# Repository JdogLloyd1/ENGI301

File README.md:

# ENGI301
Repository for ENGI301 course work Fall 2022

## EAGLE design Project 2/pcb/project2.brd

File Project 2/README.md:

# ENGI301
Repository for ENGI301 Project 2 - create a PCB that interfaces with PocketBeagle for an electronic Etch-A-Sketch. 

Repository includes PowerPoint presentation with mechanical system overview, EAGLE library/schematic/layout files, and necessary manufacturing information. 

Bill of material and manufacturing quotes from MacroFab can be found in the documentation folder.

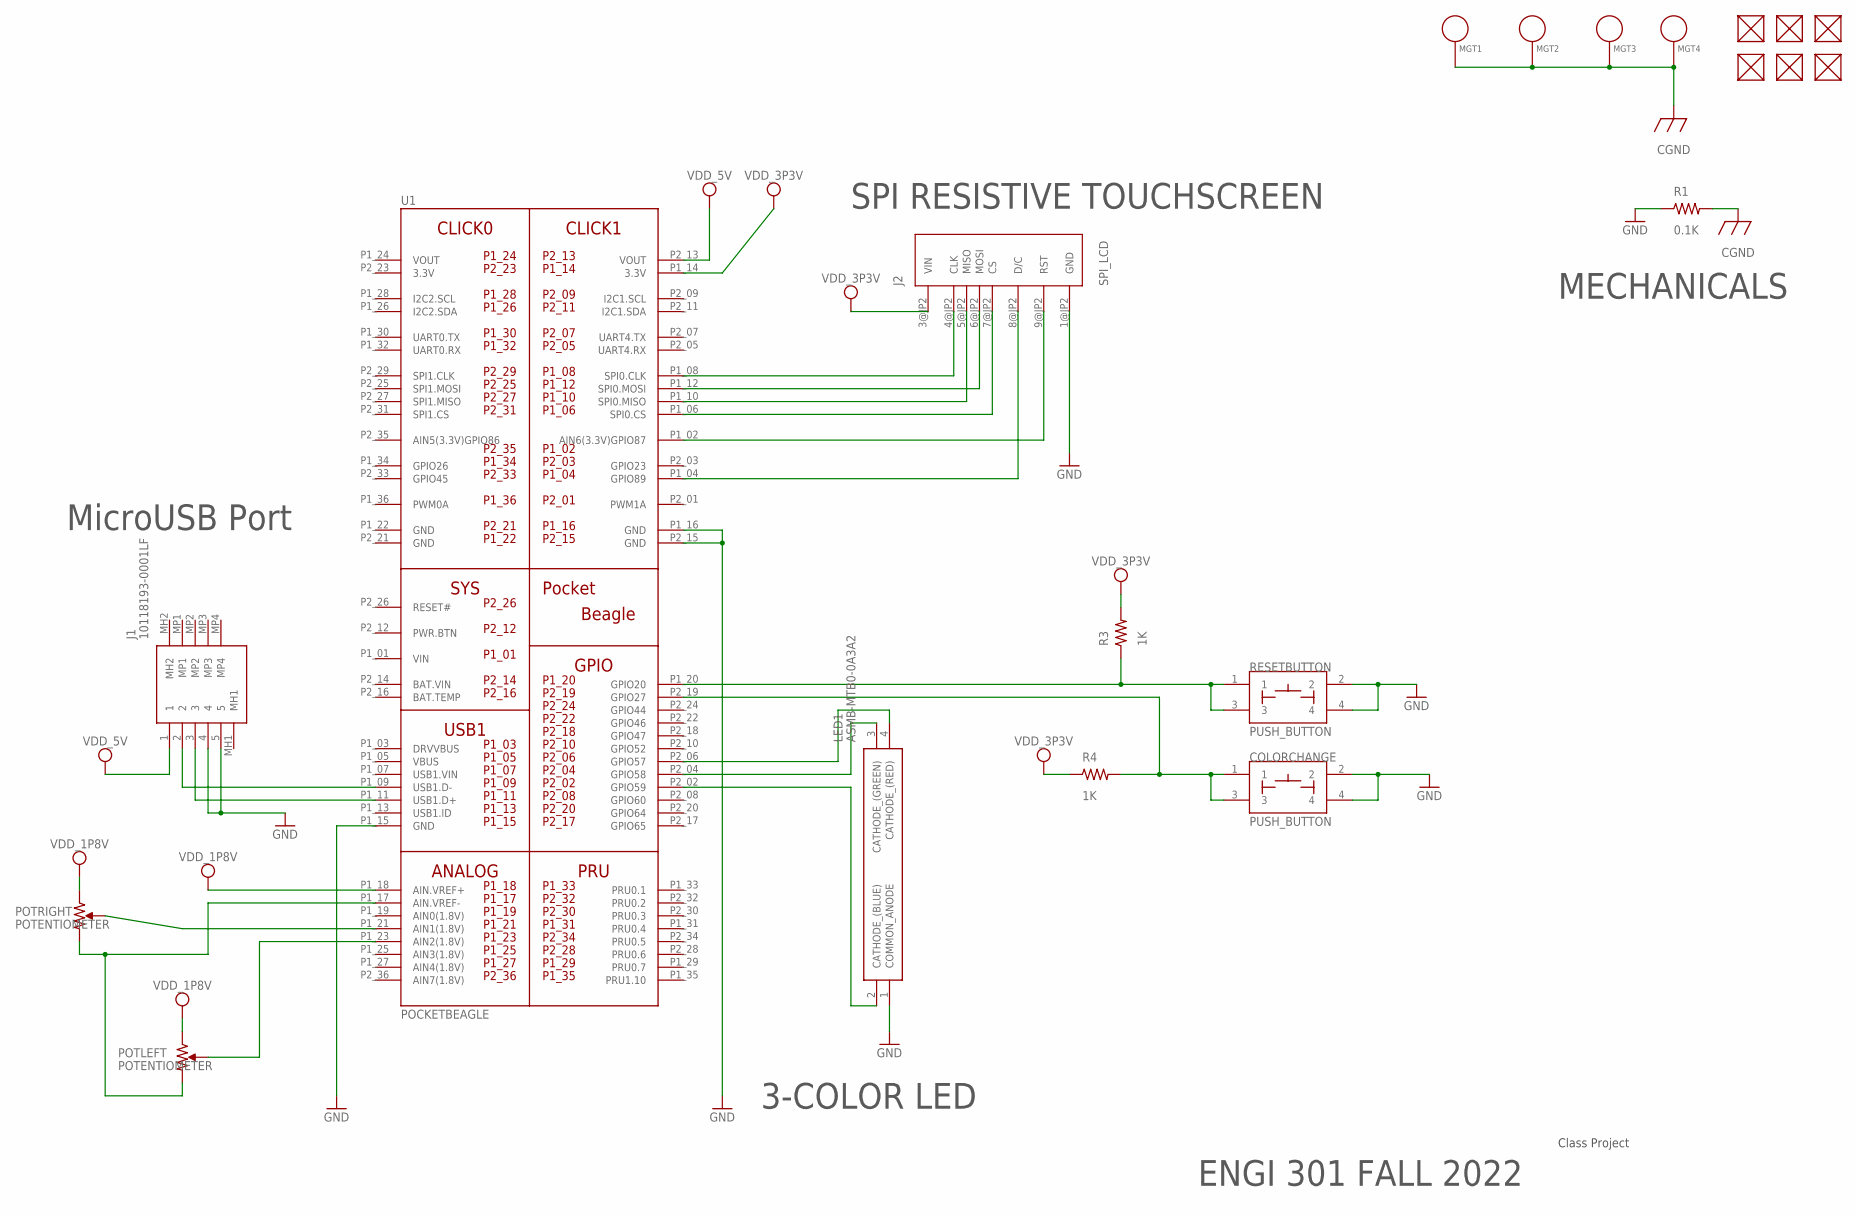
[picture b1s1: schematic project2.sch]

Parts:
COLORCHANGE: PUSH_BUTTON; BUTTON_12.5MM
FUD1, FUD2, FUD3, FUD4, FUD5, FUD6: FIDUCIAL; FIDUCIAL_40MIL
J1: 10118193-0001LF; 101181930001LF
J2: SPI_LCD; TFT_LCD_PCB
LED1: ASMB-MTB0-0A3A2; ASMBMTB00A3A2
MGT1, MGT2, MGT3, MGT4: MOUNTING_HOLE
POTLEFT: POTENTIOMETER; POT-PO90S
POTRIGHT: POTENTIOMETER; POT-PO90S
R1: 0.1K; R0603
R3, R4: 1K; R0603
RESETBUTTON: PUSH_BUTTON; BUTTON_12.5MM
U1: POCKETBEAGLE

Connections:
3.3V: U1.P2_23 (3.3V)
BAT.VIN: U1.P2_14 (BAT.VIN)
CGND: MGT1.P$1, MGT2.P$1, MGT3.P$1, MGT4.P$1, R1.2
GND: COLORCHANGE.2, COLORCHANGE.4, J1.4, J1.5, J2.1@JP2 (GND), LED1.1 (COMMON_ANODE), R1.1, RESETBUTTON.2, RESETBUTTON.4, U1.P1_15 (GND), U1.P1_16 (GND), U1.P1_22 (GND), U1.P2_15 (GND), U1.P2_21 (GND)
unnamed: POTRIGHT.S, U1.P1_21 (AIN1(1.8V))
unnamed: POTLEFT.S, U1.P1_23 (AIN2(1.8V))
unnamed: POTLEFT.CW, POTRIGHT.CW, U1.P1_17 (AIN.VREF-)
unnamed: R3.1, RESETBUTTON.1, RESETBUTTON.3, U1.P1_20 (GPIO20)
unnamed: J2.4@JP2 (CLK), U1.P1_08 (SPI0.CLK)
unnamed: J2.5@JP2 (MISO), U1.P1_10 (SPI0.MISO)
unnamed: J2.6@JP2 (MOSI), U1.P1_12 (SPI0.MOSI)
unnamed: J2.7@JP2 (CS), U1.P1_06 (SPI0.CS)
unnamed: J2.8@JP2 (D/C), U1.P1_04 (GPIO89)
unnamed: J2.9@JP2 (RST), U1.P1_02 (AIN6(3.3V)GPIO87)
unnamed: COLORCHANGE.1, COLORCHANGE.3, R4.2, U1.P2_19 (GPIO27)
unnamed: LED1.2 (CATHODE_(BLUE)), U1.P2_02 (GPIO59)
unnamed: LED1.3 (CATHODE_(GREEN)), U1.P2_04 (GPIO58)
unnamed: LED1.4 (CATHODE_(RED)), U1.P2_06 (GPIO57)
unnamed: J1.2, U1.P1_09 (USB1.D-)
unnamed: J1.3, U1.P1_11 (USB1.D+)
VDD_1P8V: POTLEFT.CCW, POTRIGHT.CCW, U1.P1_18 (AIN.VREF+)
VDD_3P3V: J2.3@JP2 (VIN), R3.2, R4.1, U1.P1_14 (3.3V)
VDD_5V: J1.1, U1.P2_13 (VOUT)
VIN: U1.P1_01 (VIN)
VOUT: U1.P1_24 (VOUT)

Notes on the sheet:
MicroUSB Port
SPI RESISTIVE TOUCHSCREEN
3-COLOR LED
Class Project
ENGI 301 FALL 2022
MECHANICALS

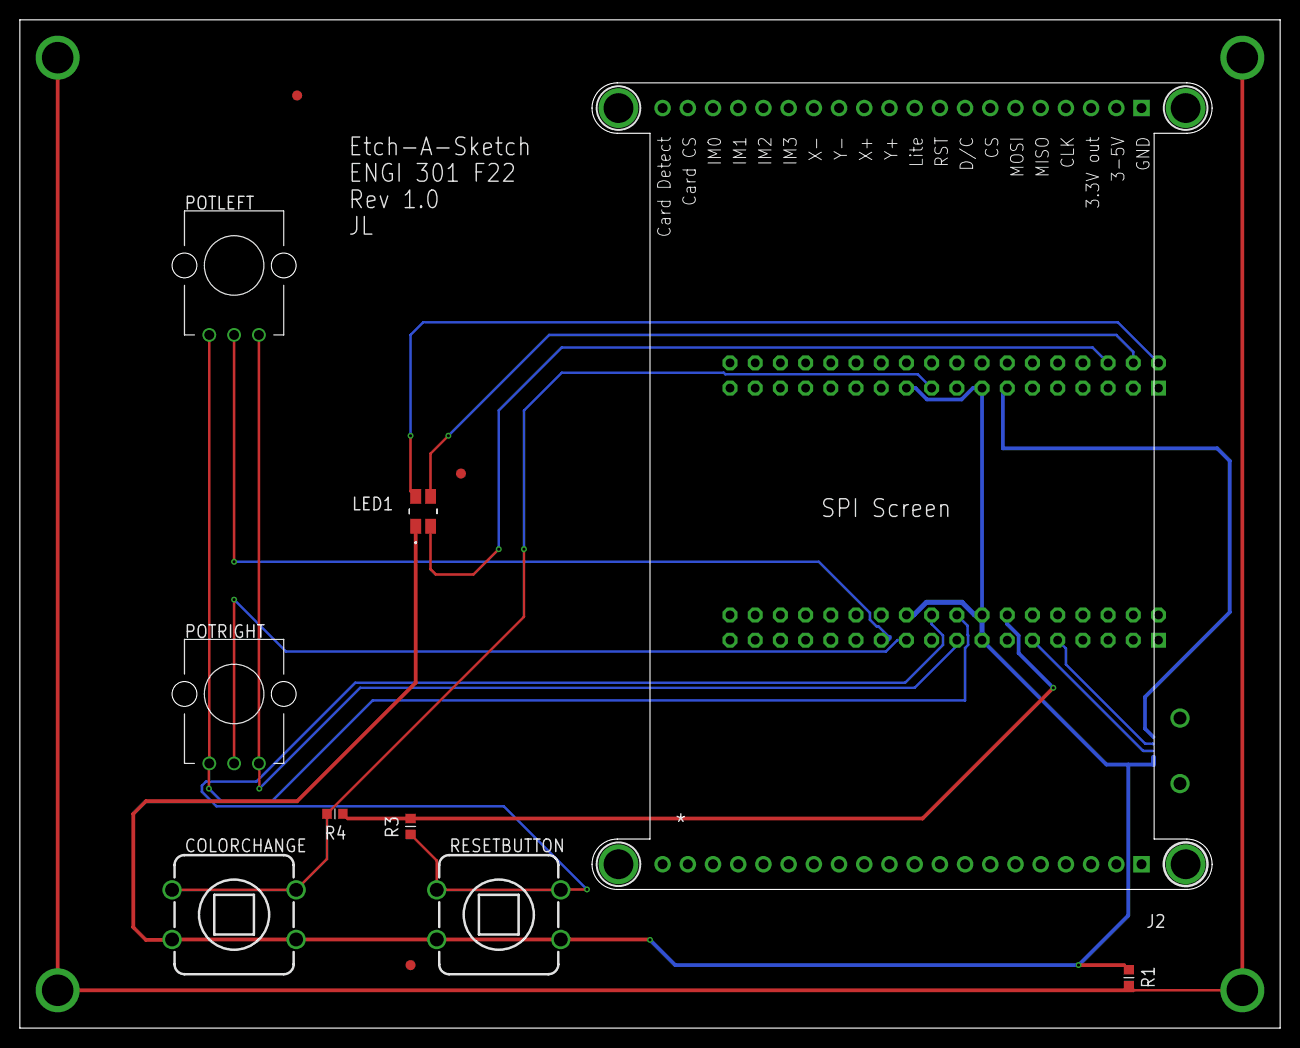
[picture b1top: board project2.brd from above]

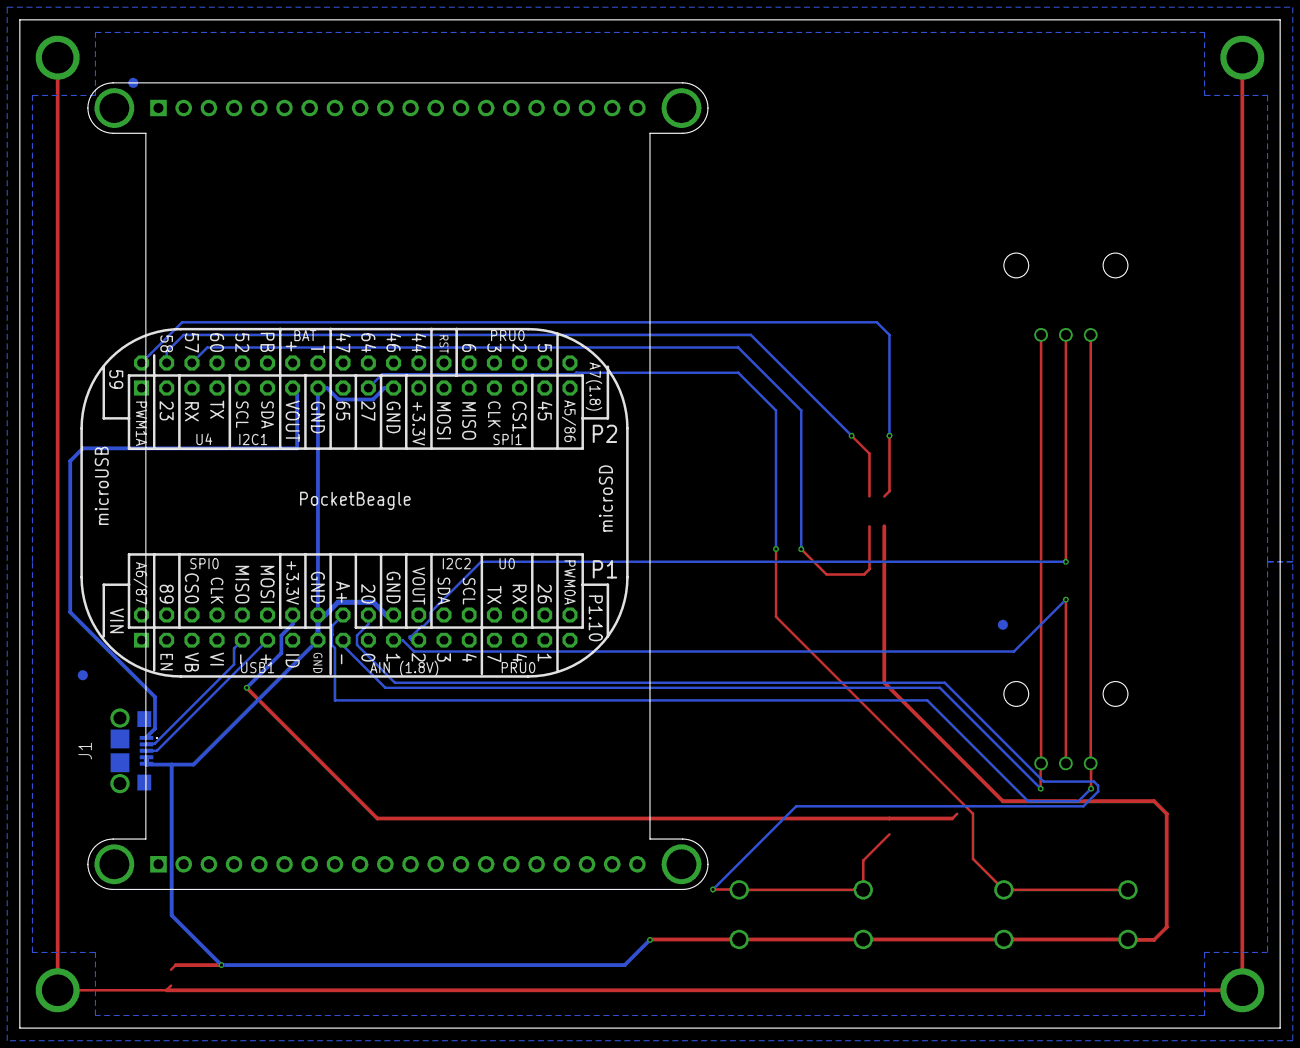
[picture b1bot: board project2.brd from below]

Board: 4 copper layers, 127.0 x 101.6 mm, 21 parts (5 on the bottom side), 21 nets.

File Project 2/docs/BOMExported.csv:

"Qty";"Value";"Device";"Package";"Parts";"Description";"DESCRIPTION";"HEIGHT";"MANUFACTURER_NAME";"MANUFACTURER_PART_NUMBER";"MOUSER_PART_NUMBER";"MOUSER_PRICE-STOCK";
"1";"0.1K";"R_R0603";"R0603";"R1";"RESISTOR, American symbol";"";"";"";"";"";"";
"1";"10118193-0001LF";"10118193-0001LF";"101181930001LF";"J1";"USB Connectors 5P MICRO USB TYPE B RECEPTACLE W/ PEGS";"USB Connectors 5P MICRO USB TYPE B RECEPTACLE W/ PEGS";"3.3mm";"Amphenol Communication Solutions";"10118193-0001LF";"649-10118193-0001LF";"https://www.mouser.co.uk/ProductDetail/Amphenol-FCI/10118193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";
"2";"1K";"R_R0603";"R0603";"R3, R4";"RESISTOR, American symbol";"";"";"";"";"";"";
"1";"ASMB-MTB0-0A3A2";"ASMB-MTB0-0A3A2";"ASMBMTB00A3A2";"LED1";"LED Tri-Color Blue/Green/Red 465nm/522nm/634nm Chip LED 4-Pin PLCC - Tape and Reel";"LED Tri-Color Blue/Green/Red 465nm/522nm/634nm Chip LED 4-Pin PLCC - Tape and Reel";"1.9mm";"Avago Technologies";"ASMB-MTB0-0A3A2";"630-ASMB-MTB0-0A3A2";"https://www.mouser.co.uk/ProductDetail/Broadcom-Avago/ASMB-M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";
"6";"FIDUCIAL";"FIDUCIAL";"FIDUCIAL_40MIL";"FUD1, FUD2, FUD3, FUD4, FUD5, FUD6";"";"";"";"";"";"";"";
"4";"MOUNTING_HOLE";"MOUNTING_HOLE";"MOUNTING_HOLE";"MGT1, MGT2, MGT3, MGT4";"Chassis Mounting Hole w/GND connection ability";"";"";"";"";"";"";
"1";"POCKETBEAGLE";"POCKETBEAGLE";"POCKETBEAGLE";"U1";"";"";"";"";"";"";"";
"2";"POTENTIOMETER";"POTENTIOMETER";"POT-PO90S";"POTLEFT, POTRIGHT";"Potentiometer - Examples:";"";"";"";"";"";"";
"2";"PUSH_BUTTON";"PUSH_BUTTON";"BUTTON_12.5MM";"COLORCHANGE, RESETBUTTON";"";"";"";"";"";"";"";
"1";"SPI_LCD";"SPI_LCD";"TFT_LCD_PCB";"J2";"";"";"";"";"";"";"";

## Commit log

2022-09-21 simple calc test push
2022-09-22 simple calc commit v1
2022-09-25 mmap
2022-09-27 Assignment 4 Files
2022-10-05 updated parts list
2022-10-06 class files update
2022-11-09 moved file
2022-11-09 fleshing out more outline
2022-12-10 folders
2022-12-10 readme
2022-12-11 temp save
2022-12-12 Sunday night update
    SPI board throwing errors, MacroFab website cannot process .brd as a result.
2022-12-12 block diagram update
2022-12-12 added run script
2022-12-12 updated block diagram Proj 1
2022-12-17 proposal update
